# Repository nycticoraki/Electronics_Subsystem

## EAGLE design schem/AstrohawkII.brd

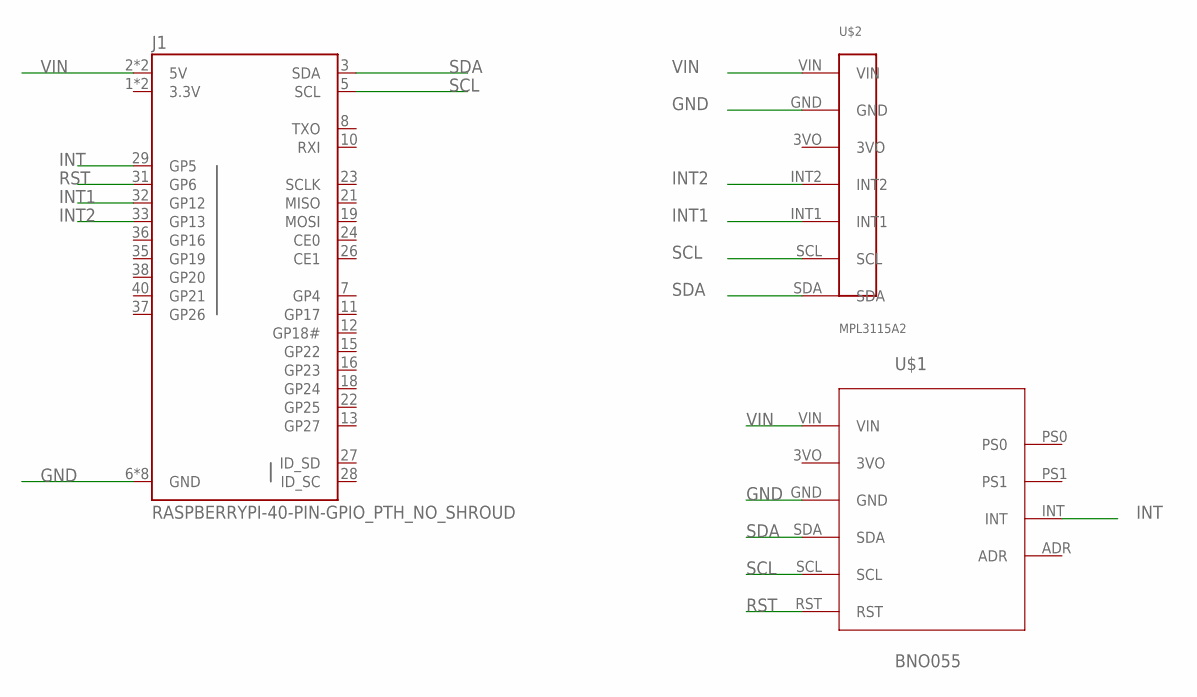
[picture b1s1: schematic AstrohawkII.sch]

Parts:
J1: RASPBERRYPI-40-PIN-GPIO_PTH_NO_SHROUD; 2X20
U$1: BNO055
U$2: MPL3115A2

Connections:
3.3V: J1.1 (3.3V), J1.17 (3.3V)
GND: J1.6 (GND), J1.9 (GND), J1.14 (GND), J1.20 (GND), J1.25 (GND), J1.30 (GND), J1.34 (GND), J1.39 (GND), U$1.GND, U$2.GND
INT: J1.29 (GP5), U$1.INT
INT1: J1.32 (GP12), U$2.INT1
INT2: J1.33 (GP13), U$2.INT2
RST: J1.31 (GP6), U$1.RST
SCL: J1.5 (SCL), U$1.SCL, U$2.SCL
SDA: J1.3 (SDA), U$1.SDA, U$2.SDA
VIN: J1.2 (5V), J1.4 (5V), U$1.VIN, U$2.VIN

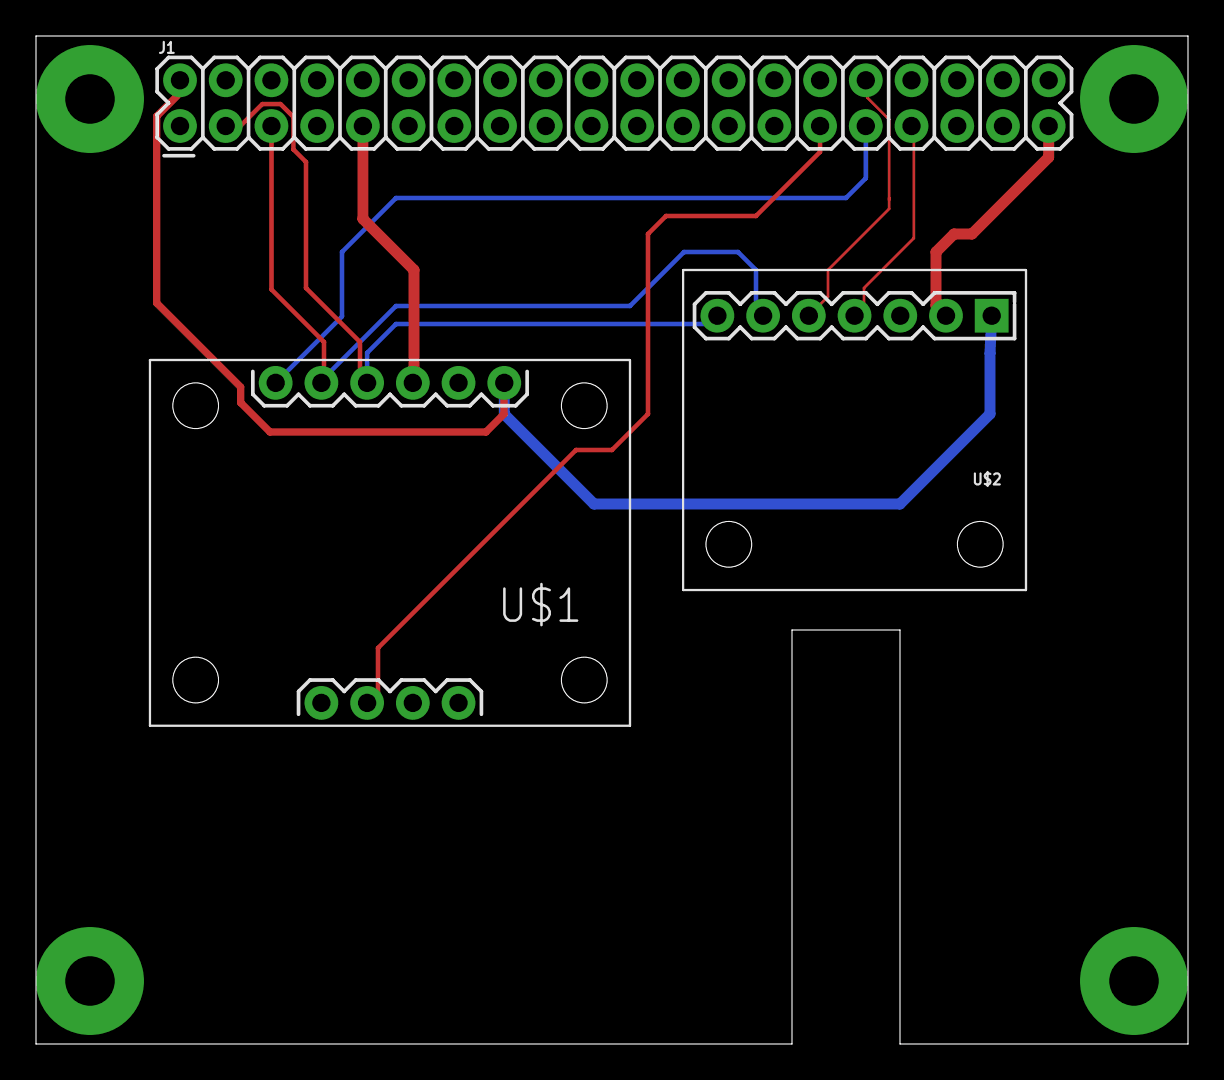
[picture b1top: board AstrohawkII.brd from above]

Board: 2 copper layers, 64.0 x 56.0 mm, 3 parts (0 on the bottom side), 9 nets.

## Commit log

2019-10-31 adds circuit diagram from Jaki
2019-10-31 adds system block diagram
2020-02-19 adds an eagle library for pcb
2020-02-20 Eagle schematic for PCB
2020-02-20 updates eagle schematic and board
2020-02-20 fixes holes for raspberry pi
    This change fixes the holes for the raspberry pi, adds
    measurement lines showing the correct dimensions, and
    updates the IMU part because the pins were backwards on
    the symbol.
2020-02-21 finishes placement and routes wires
    This change places the raspberry pi header in the
    correct location. It also routes wires to all
    relevant locations. For some reason the raspberry
    pi header we're using wants to connect all of the
    power and ground pins together, but that shouldn't
    be necessary, so I've left them unconnected and
2020-02-23 adds finishing touches to pcb design
    1. Altimeter device (package/symbol) added with drill holes for screws
    2. Drill holes and silk screen updated for IMU device
    3. Hole cutout added to account for the camera cable
    4. Copper re-routed for Altimeter
2020-09-11 adds files for setting up imu sensor
2020-09-25 added web folder with some test code - Note this only works on my pi since I've set it up for my sensor, changing the sensorIO.py file and adding a class for each sensor can be used instead.
2020-09-25 added flask server with working example
2020-09-25 removed temp files and changed graph toa sliding window
2020-09-25 changed some small stuff
2020-10-02 added temporary folder for testing out flaskio
2020-10-03 rewrote using flaskio and socketio
2020-10-09 removes static ip from source.js and removes pycache
    This change removes the dependency on a static ip
    address and it removes binary files created by python.
2020-10-09 removes hardcoded ip in source.js for flaskio
2020-10-09 Added older tests
    Moved older test files into test/other_imu_tests/
2020-10-16 Works with imu and altimeter sensor now
    Added support for imu and altimeter but only testing temperature and altitude respectively
    Added Singleton Pattern for sensors so only one can be instantiated at once and they use the same i2c object as it itself can only be instantiated once
    Issues:
    sensor has some issue with timing where querying a sensor value at the wrong time can cause a spike in value.
    lowering the number of requests per second causes this to happen less.
2020-10-16 Cleaned up some stuff
    Issue with altimeter sending data slowly and the timing issues mentioned prior still exist
2020-10-22 updated i2c board constructor
2020-10-23 imu file updates
2020-11-06 adds dummy sensor to sensorIO in web directory
    This change abstracts out sensor class creation
    to allow for a base class and a dummy sensor for
    those w/o a range sensor.
2020-11-06 Fixed Issue
    Fixed an issue with one of the disconnect functions
2020-11-06 Added more sensor options
    Can now select the values to be graphed by the sensor
    - Need to limit certain values to specific graphs since they are either an array of size 3 or 4
    Changing the sensor and test fields will now force a disconnect until I have a better solution ready
    Added a window that constantly prints raw data values for the current sensor.
2020-11-26 adds sensor server and client for ipc
    This change adds a sensor server and
    a sensor client using asyncio. The
    server and client model use unix
    sockets for inter process communication.
    This allows the web streaming of sensor
    data to be independent of the csv file

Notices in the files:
parts and their libraries:
SparkFun-Connectors: Licensing: Creative Commons ShareAlike 4.0 International - https://creativecommons.org/licenses/by-sa/4.0
